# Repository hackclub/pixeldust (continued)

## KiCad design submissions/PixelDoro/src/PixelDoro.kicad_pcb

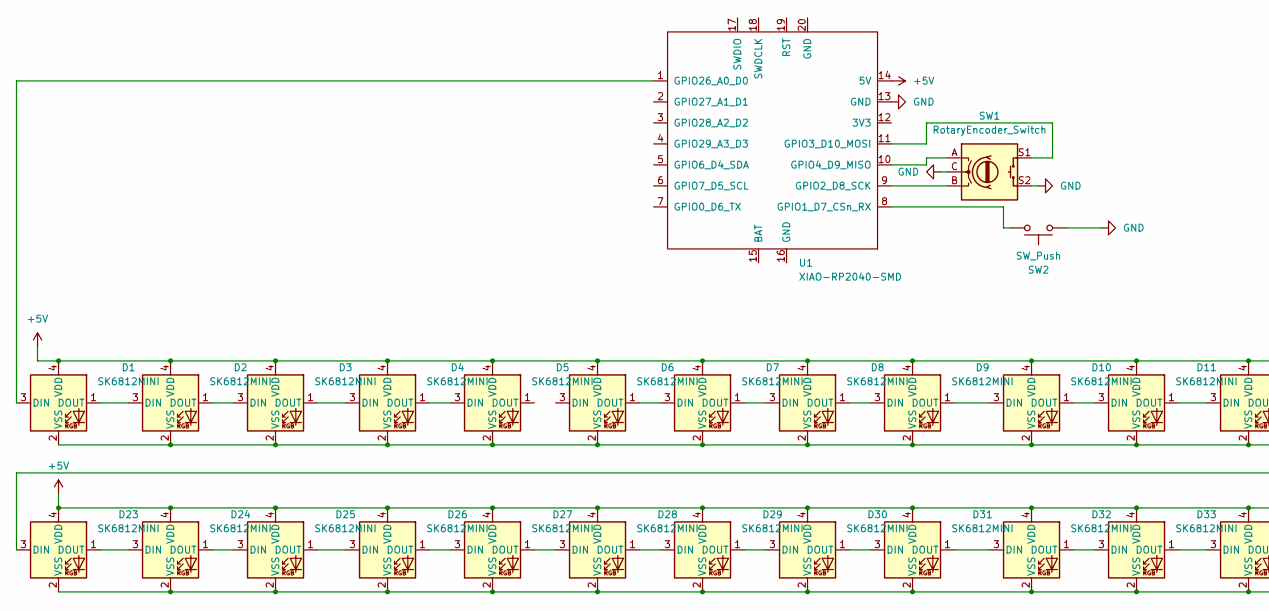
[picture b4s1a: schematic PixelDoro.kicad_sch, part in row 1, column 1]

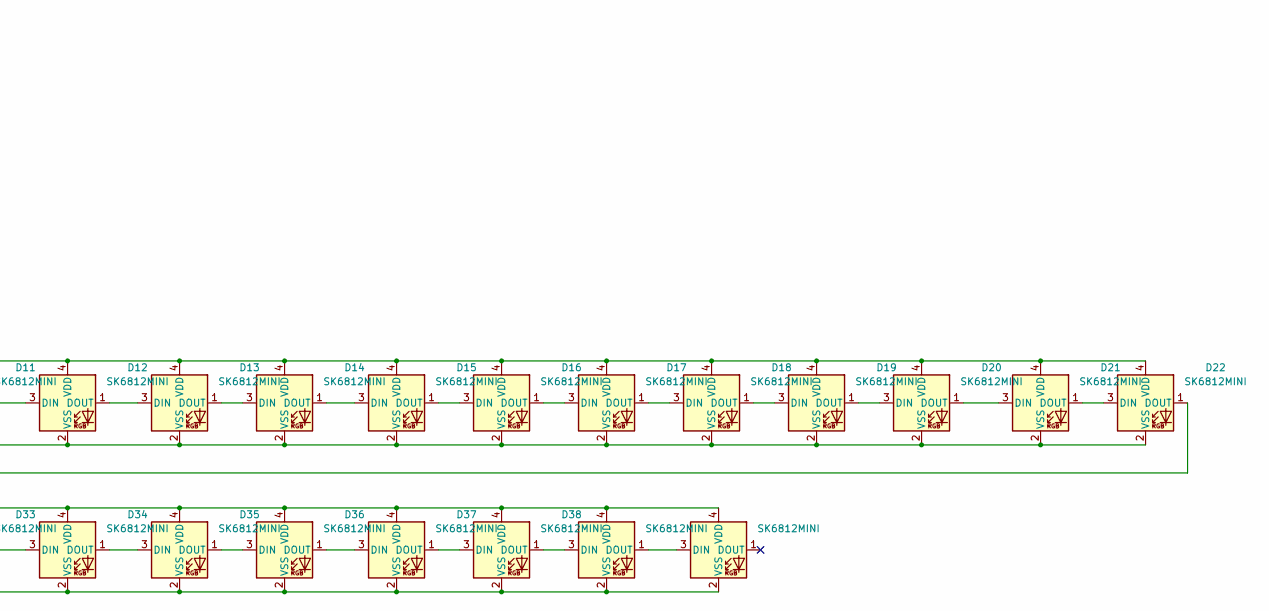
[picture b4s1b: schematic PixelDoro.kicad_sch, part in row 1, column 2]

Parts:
D1, D2, D3, D4, D5, D6, D7, D8, D9, D10, D11, D12, D13, D14, D15, D16, D17, D18, D19, D20, D21, D22, D23, D24, D25, D26, D27, D28, D29, D30, D31, D32, D33, D34, D35, D36, D37, D38, D39, D40: SK6812MINI; LED_SK6812MINI_PLCC4_3.5x3.5mm_P1.75mm
SW1: RotaryEncoder_Switch; RotaryEncoder_Alps_EC11E_Vertical_H20mm_CircularMountingHol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
SW2: SW_Push; SW_PUSH-12mm
U1: XIAO-RP2040-SMD

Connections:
+5V: D1.4 (VDD), D2.4 (VDD), D3.4 (VDD), D4.4 (VDD), D5.4 (VDD), D6.4 (VDD), D7.4 (VDD), D8.4 (VDD), D9.4 (VDD), D10.4 (VDD), D11.4 (VDD), D12.4 (VDD), D13.4 (VDD), D14.4 (VDD), D15.4 (VDD), D16.4 (VDD), D17.4 (VDD), D18.4 (VDD), D19.4 (VDD), D20.4 (VDD), D21.4 (VDD), D22.4 (VDD), D23.4 (VDD), D24.4 (VDD), D25.4 (VDD), D26.4 (VDD), D27.4 (VDD), D28.4 (VDD), D29.4 (VDD), D30.4 (VDD), D31.4 (VDD), D32.4 (VDD), D33.4 (VDD), D34.4 (VDD), D35.4 (VDD), D36.4 (VDD), D37.4 (VDD), D38.4 (VDD), D39.4 (VDD), D40.4 (VDD), U1.14 (5V); also elsewhere on the board
GND: SW1.C, SW1.S2, SW2.1, U1.13 (GND)
unnamed: D1.3 (DIN), U1.1 (GPIO26_A0_D0)
unnamed: D1.1 (DOUT), D2.3 (DIN)
unnamed: D1.2 (VSS), D2.2 (VSS), D3.2 (VSS), D4.2 (VSS), D5.2 (VSS), D6.2 (VSS), D7.2 (VSS), D8.2 (VSS), D9.2 (VSS), D10.2 (VSS), D11.2 (VSS), D12.2 (VSS), D13.2 (VSS), D14.2 (VSS), D15.2 (VSS), D16.2 (VSS), D17.2 (VSS), D18.2 (VSS), D19.2 (VSS), D20.2 (VSS), D21.2 (VSS), D22.2 (VSS)
unnamed: D2.1 (DOUT), D3.3 (DIN)
unnamed: D3.1 (DOUT), D4.3 (DIN)
unnamed: D4.1 (DOUT), D5.3 (DIN)
unnamed: D6.1 (DOUT), D7.3 (DIN)
unnamed: D7.1 (DOUT), D8.3 (DIN)
unnamed: D8.1 (DOUT), D9.3 (DIN)
unnamed: D9.1 (DOUT), D10.3 (DIN)
unnamed: D10.1 (DOUT), D11.3 (DIN)
unnamed: D11.1 (DOUT), D12.3 (DIN)
unnamed: D12.1 (DOUT), D13.3 (DIN)
unnamed: D13.1 (DOUT), D14.3 (DIN)
unnamed: D14.1 (DOUT), D15.3 (DIN)
unnamed: D15.1 (DOUT), D16.3 (DIN)
unnamed: D16.1 (DOUT), D17.3 (DIN)
unnamed: D17.1 (DOUT), D18.3 (DIN)
unnamed: D18.1 (DOUT), D19.3 (DIN)
unnamed: D19.1 (DOUT), D20.3 (DIN)
unnamed: D20.1 (DOUT), D21.3 (DIN)
unnamed: D21.1 (DOUT), D22.3 (DIN)
unnamed: D22.1 (DOUT), D23.3 (DIN)
unnamed: D23.1 (DOUT), D24.3 (DIN)
unnamed 26: D23.2 (VSS), D24.2 (VSS), D25.2 (VSS), D26.2 (VSS), D27.2 (VSS), D28.2 (VSS), D29.2 (VSS), D30.2 (VSS), D31.2 (VSS), D32.2 (VSS), D33.2 (VSS), D34.2 (VSS), D35.2 (VSS), D36.2 (VSS), D37.2 (VSS), D38.2 (VSS), D39.2 (VSS), D40.2 (VSS); also elsewhere on the board
unnamed: D24.1 (DOUT), D25.3 (DIN)
unnamed: D25.1 (DOUT), D26.3 (DIN)
unnamed: D26.1 (DOUT), D27.3 (DIN)
unnamed: D27.1 (DOUT), D28.3 (DIN)
unnamed: D28.1 (DOUT), D29.3 (DIN)
unnamed: D29.1 (DOUT), D30.3 (DIN)
unnamed: D30.1 (DOUT), D31.3 (DIN)
unnamed: D31.1 (DOUT), D32.3 (DIN)
unnamed: D32.1 (DOUT), D33.3 (DIN)
unnamed: D33.1 (DOUT), D34.3 (DIN)
unnamed: D34.1 (DOUT), D35.3 (DIN)
unnamed: D35.1 (DOUT), D36.3 (DIN)
unnamed: D36.1 (DOUT), D37.3 (DIN)
unnamed: D37.1 (DOUT), D38.3 (DIN)
unnamed 41: D38.1 (DOUT), D39.3 (DIN); also elsewhere on the board
unnamed: D39.1 (DOUT), D40.3 (DIN)
unnamed: SW2.2, U1.8 (GPIO1_D7_CSn_RX)
unnamed: SW1.B, U1.9 (GPIO2_D8_SCK)
unnamed: SW1.S1, U1.11 (GPIO3_D10_MOSI)
unnamed: SW1.A, U1.10 (GPIO4_D9_MISO)

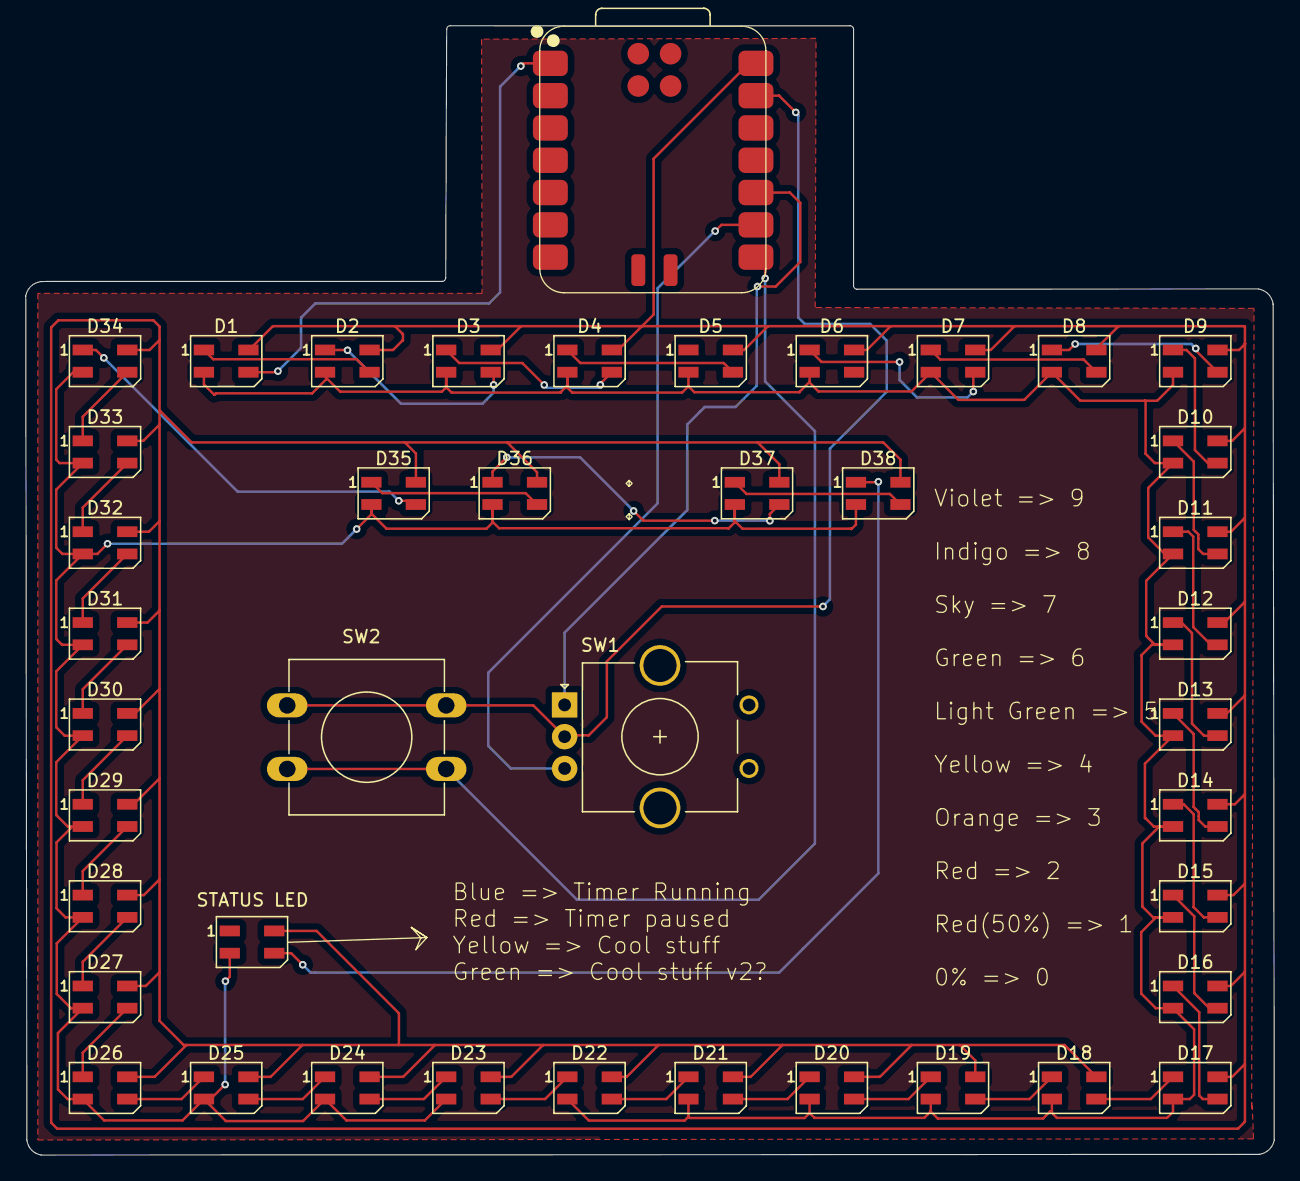
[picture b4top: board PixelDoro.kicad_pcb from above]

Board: 2 copper layers, 98.2 x 88.8 mm, 42 parts (0 on the bottom side), 45 nets.

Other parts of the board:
STATUS LED: Status LED; LED_SK6812MINI_PLCC4_3.5x3.5mm_P1.75mm

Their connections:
+5V: STATUS LED.4 (VDD); also elsewhere on the board
unnamed 26: STATUS LED.2 (VSS); also elsewhere on the board
unnamed 41: STATUS LED.3 (DIN); also elsewhere on the board

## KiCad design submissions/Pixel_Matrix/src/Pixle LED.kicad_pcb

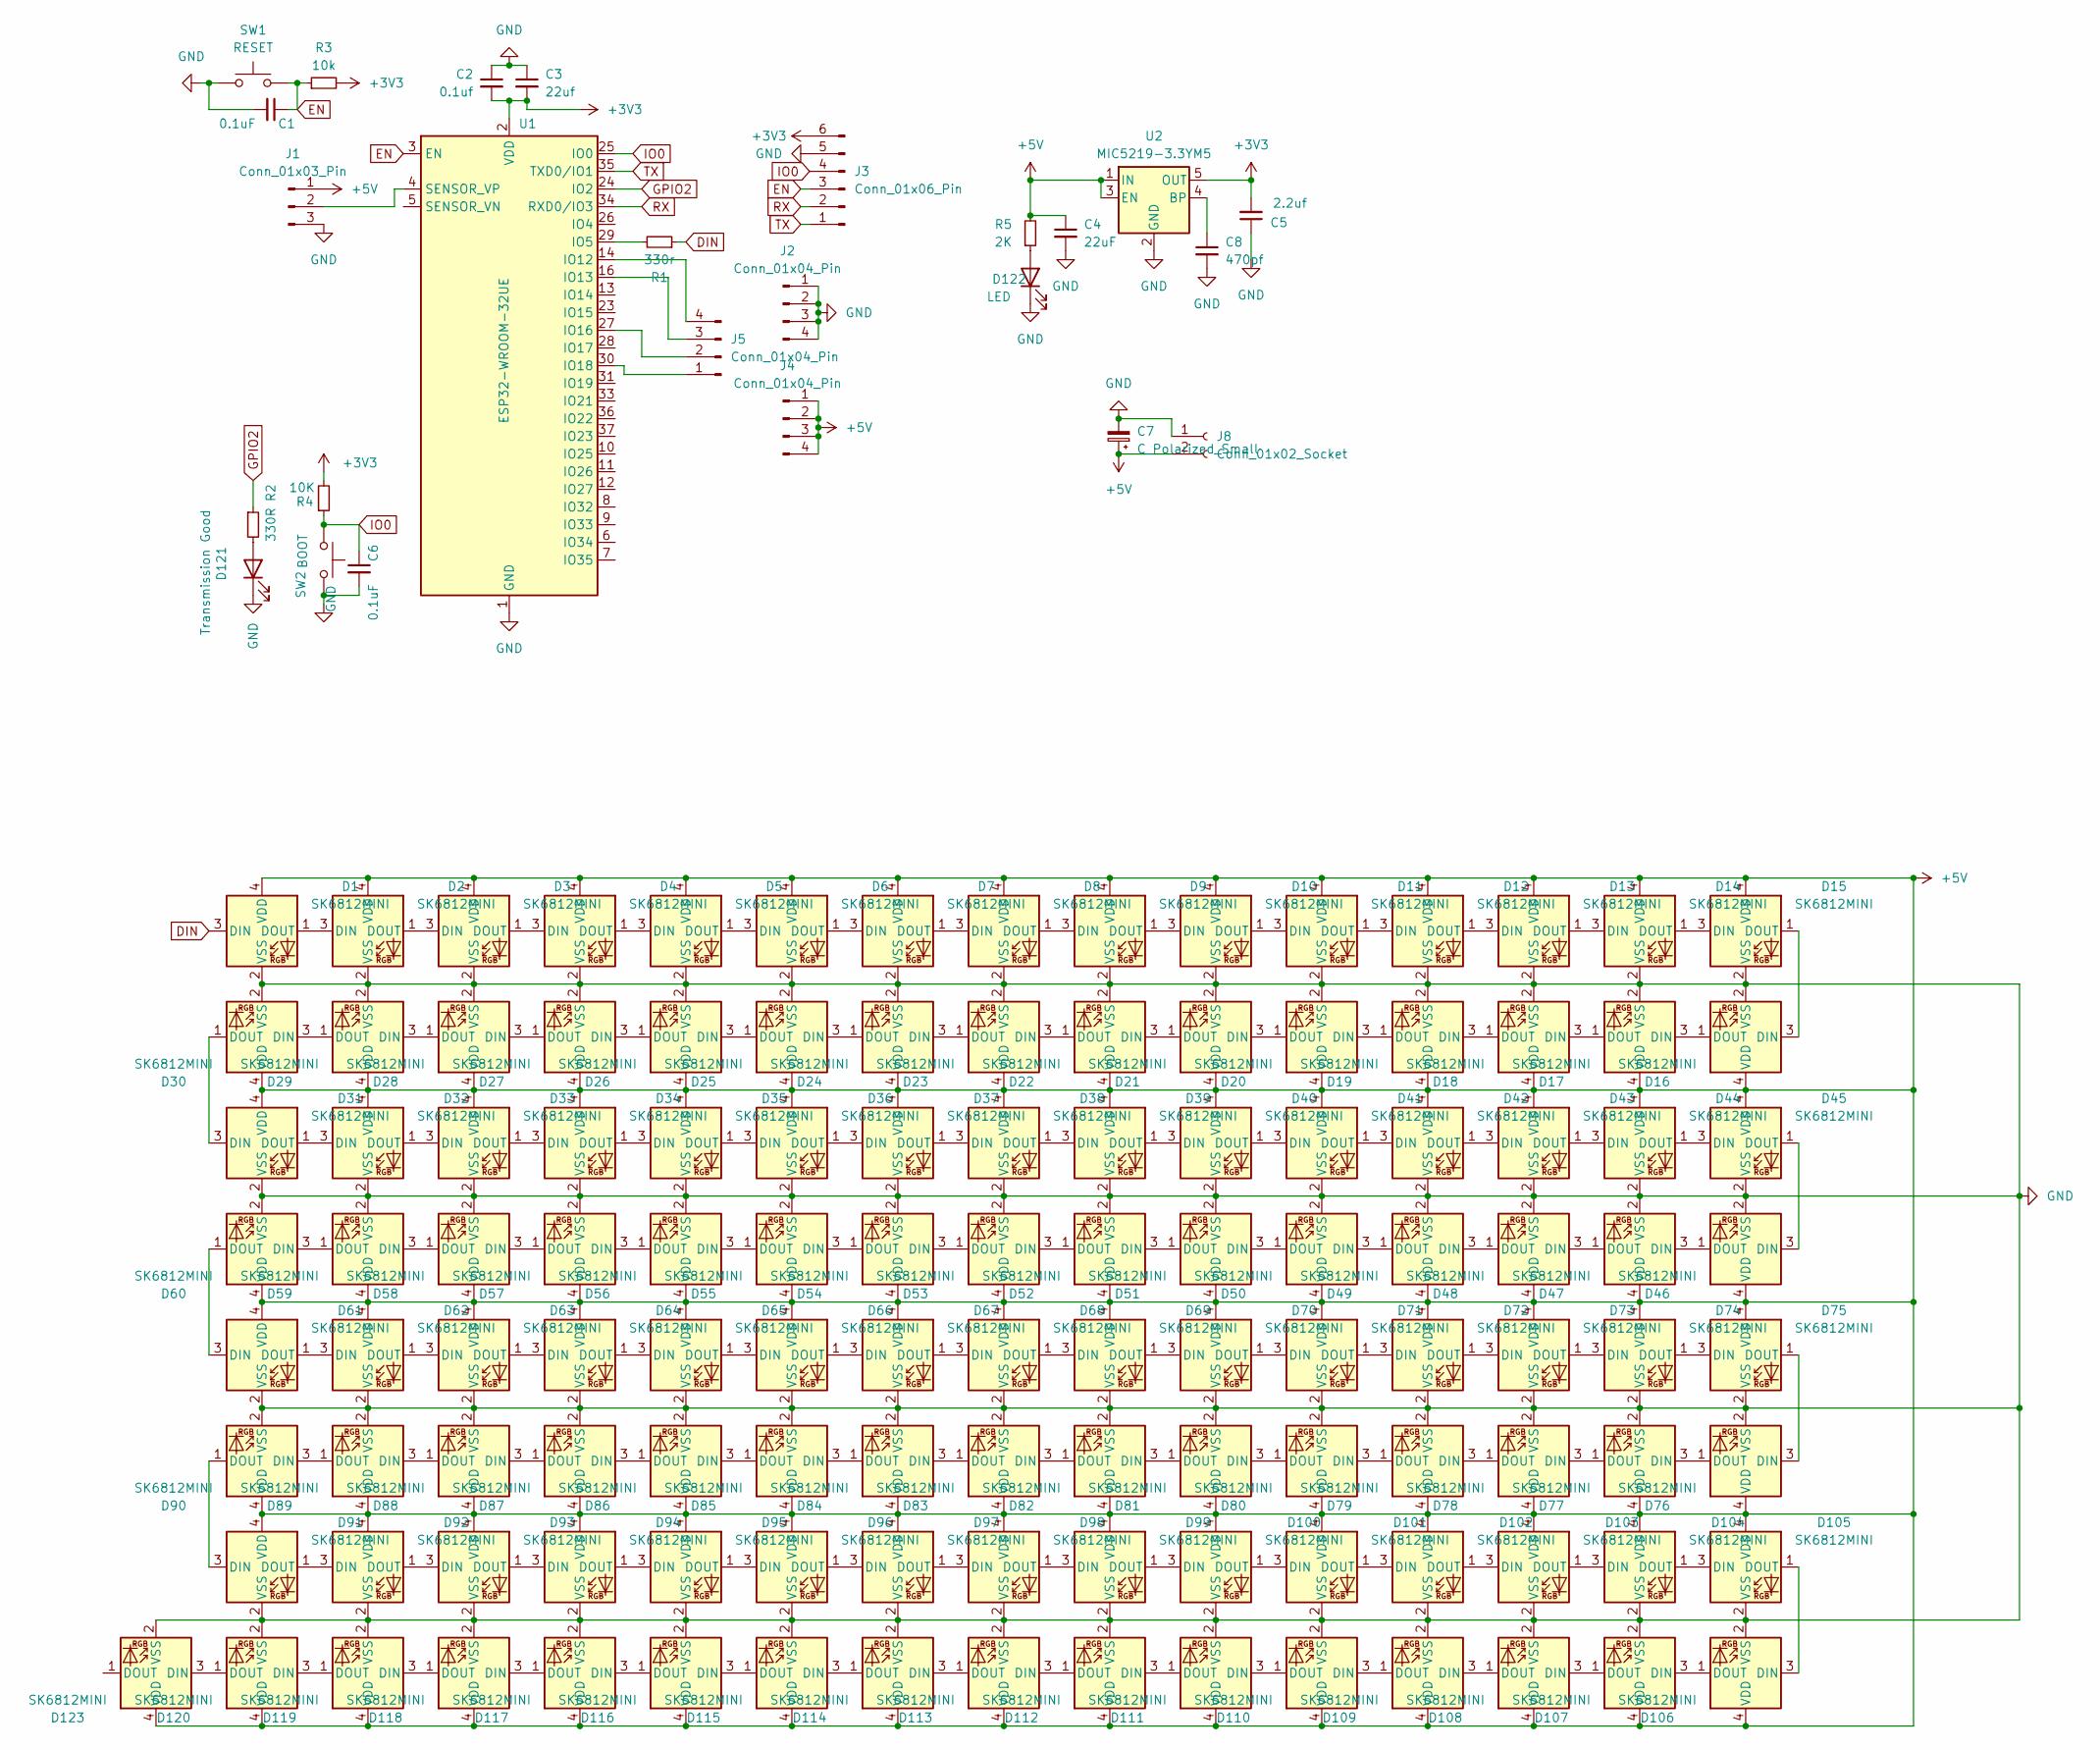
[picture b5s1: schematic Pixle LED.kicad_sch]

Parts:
C1, C6: 0.1uF; C_0805_2012Metric_Pad1.18x1.45mm_HandSolder
C2: 0.1uf; C_0805_2012Metric_Pad1.18x1.45mm_HandSolder
C3: 22uf; C_0805_2012Metric_Pad1.18x1.45mm_HandSolder
C4: 22uF; C_0805_2012Metric_Pad1.18x1.45mm_HandSolder
C5: 2.2uf; C_0603_1608Metric_Pad1.08x0.95mm_HandSolder
C7: C_Polarized_Small; CP_Radial_D8.0mm_P3.50mm
C8: 470pf; C_0603_1608Metric_Pad1.08x0.95mm_HandSolder
D1, D2, D3, D4, D5, D6, D7, D8, D9, D10, D11, D12, D13, D14, D15, D16, D17, D18, D19, D20, D21, D22, D23, D24, D25, D26, D27, D28, D29, D30, D31, D32, D33, D34, D35, D36, D37, D38, D39, D40, D41, D42, D43, D44, D45, D46, D47, D48, D49, D50, D51, D52, D53, D54, D55, D56, D57, D58, D59, D60, D61, D62, D63, D64, D65, D66, D67, D68, D69, D70, D71, D72, D73, D74, D75, D76, D77, D78, D79, D80, D81, D82, D83, D84, D85, D86, D87, D88, D89, D90, D91, D92, D93, D94, D95, D96, D97, D98, D99, D100, D101, D102, D103, D104, D105, D106, D107, D108, D109, D110, D111, D112, D113, D114, D115, D116, D117, D118, D119, D120, D123: SK6812MINI; LED_SK6812MINI_PLCC4_3.5x3.5mm_P1.75mm
D121: Transmission Good; LED_0805_2012Metric_Pad1.15x1.40mm_HandSolder
D122: LED; LED_0805_2012Metric_Pad1.15x1.40mm_HandSolder
J1: Conn_01x03_Pin; PinHeader_1x03_P2.54mm_Vertical
J2, J4, J5: Conn_01x04_Pin; PinHeader_1x04_P2.54mm_Vertical
J3: Conn_01x06_Pin; PinHeader_1x06_P2.54mm_Vertical
J8: Conn_01x02_Socket; TerminalBlock_MaiXu_MX126-5.0-02P_1x02_P5.00mm
R1: 330r; R_0603_1608Metric_Pad0.98x0.95mm_HandSolder
R2: 330R; R_0805_2012Metric_Pad1.20x1.40mm_HandSolder
R3: 10k; R_0805_2012Metric_Pad1.20x1.40mm_HandSolder
R4: 10K; R_0805_2012Metric_Pad1.20x1.40mm_HandSolder
R5: 2K; R_0805_2012Metric_Pad1.20x1.40mm_HandSolder
SW1: RESET; SW_Push_SPST_NO_Alps_SKRK
SW2: BOOT; SW_Push_SPST_NO_Alps_SKRK
U1: ESP32-WROOM-32UE; ESP32-WROOM-32E
U2: MIC5219-3.3YM5; SOT-23-5

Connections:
+3V3: C2.2, C3.2, C5.2, J3.6, R3.2, R4.2, U1.2 (VDD), U2.5 (OUT)
+5V: C4.1, C7.1, D1.4 (VDD), D2.4 (VDD), D3.4 (VDD), D4.4 (VDD), D5.4 (VDD), D6.4 (VDD), D7.4 (VDD), D8.4 (VDD), D9.4 (VDD), D10.4 (VDD), D11.4 (VDD), D12.4 (VDD), D13.4 (VDD), D14.4 (VDD), D15.4 (VDD), D16.4 (VDD), D17.4 (VDD), D18.4 (VDD), D19.4 (VDD), D20.4 (VDD), D21.4 (VDD), D22.4 (VDD), D23.4 (VDD), D24.4 (VDD), D25.4 (VDD), D26.4 (VDD), D27.4 (VDD), D28.4 (VDD), D29.4 (VDD), D30.4 (VDD), D31.4 (VDD), D32.4 (VDD), D33.4 (VDD), D34.4 (VDD), D35.4 (VDD), D36.4 (VDD), D37.4 (VDD), D38.4 (VDD), D39.4 (VDD), D40.4 (VDD), D41.4 (VDD), D42.4 (VDD), D43.4 (VDD), D44.4 (VDD), D45.4 (VDD), D46.4 (VDD), D47.4 (VDD), D48.4 (VDD), D49.4 (VDD), D50.4 (VDD), D51.4 (VDD), D52.4 (VDD), D53.4 (VDD), D54.4 (VDD), D55.4 (VDD), D56.4 (VDD), D57.4 (VDD), D58.4 (VDD), D59.4 (VDD), D60.4 (VDD), D61.4 (VDD), D62.4 (VDD), D63.4 (VDD), D64.4 (VDD), D65.4 (VDD), D66.4 (VDD), D67.4 (VDD), D68.4 (VDD), D69.4 (VDD), D70.4 (VDD), D71.4 (VDD), D72.4 (VDD), D73.4 (VDD), D74.4 (VDD), D75.4 (VDD), D76.4 (VDD), D77.4 (VDD), D78.4 (VDD), D79.4 (VDD), D80.4 (VDD), D81.4 (VDD), D82.4 (VDD), D83.4 (VDD), D84.4 (VDD), D85.4 (VDD), D86.4 (VDD), D87.4 (VDD), D88.4 (VDD), D89.4 (VDD), D90.4 (VDD), D91.4 (VDD), D92.4 (VDD), D93.4 (VDD), D94.4 (VDD), D95.4 (VDD), D96.4 (VDD), D97.4 (VDD), D98.4 (VDD), D99.4 (VDD), D100.4 (VDD), D101.4 (VDD), D102.4 (VDD), D103.4 (VDD), D104.4 (VDD), D105.4 (VDD), D106.4 (VDD), D107.4 (VDD), D108.4 (VDD), D109.4 (VDD), D110.4 (VDD), D111.4 (VDD), D112.4 (VDD), D113.4 (VDD), D114.4 (VDD), D115.4 (VDD), D116.4 (VDD), D117.4 (VDD), D118.4 (VDD), D119.4 (VDD), D120.4 (VDD), D123.4 (VDD), J1.1, J4.1, J4.2, J4.3, J4.4, J8.2, R5.2, U2.1 (IN), U2.3 (EN)
DIN: D1.3 (DIN), R1.1
EN: C1.1, J3.3, R3.1, SW1.2, U1.3 (EN)
GND: C1.2, C2.1, C3.1, C4.2, C5.1, C6.2, C7.2, C8.2, D1.2 (VSS), D2.2 (VSS), D3.2 (VSS), D4.2 (VSS), D5.2 (VSS), D6.2 (VSS), D7.2 (VSS), D8.2 (VSS), D9.2 (VSS), D10.2 (VSS), D11.2 (VSS), D12.2 (VSS), D13.2 (VSS), D14.2 (VSS), D15.2 (VSS), D16.2 (VSS), D17.2 (VSS), D18.2 (VSS), D19.2 (VSS), D20.2 (VSS), D21.2 (VSS), D22.2 (VSS), D23.2 (VSS), D24.2 (VSS), D25.2 (VSS), D26.2 (VSS), D27.2 (VSS), D28.2 (VSS), D29.2 (VSS), D30.2 (VSS), D31.2 (VSS), D32.2 (VSS), D33.2 (VSS), D34.2 (VSS), D35.2 (VSS), D36.2 (VSS), D37.2 (VSS), D38.2 (VSS), D39.2 (VSS), D40.2 (VSS), D41.2 (VSS), D42.2 (VSS), D43.2 (VSS), D44.2 (VSS), D45.2 (VSS), D46.2 (VSS), D47.2 (VSS), D48.2 (VSS), D49.2 (VSS), D50.2 (VSS), D51.2 (VSS), D52.2 (VSS), D53.2 (VSS), D54.2 (VSS), D55.2 (VSS), D56.2 (VSS), D57.2 (VSS), D58.2 (VSS), D59.2 (VSS), D60.2 (VSS), D61.2 (VSS), D62.2 (VSS), D63.2 (VSS), D64.2 (VSS), D65.2 (VSS), D66.2 (VSS), D67.2 (VSS), D68.2 (VSS), D69.2 (VSS), D70.2 (VSS), D71.2 (VSS), D72.2 (VSS), D73.2 (VSS), D74.2 (VSS), D75.2 (VSS), D76.2 (VSS), D77.2 (VSS), D78.2 (VSS), D79.2 (VSS), D80.2 (VSS), D81.2 (VSS), D82.2 (VSS), D83.2 (VSS), D84.2 (VSS), D85.2 (VSS), D86.2 (VSS), D87.2 (VSS), D88.2 (VSS), D89.2 (VSS), D90.2 (VSS), D91.2 (VSS), D92.2 (VSS), D93.2 (VSS), D94.2 (VSS), D95.2 (VSS), D96.2 (VSS), D97.2 (VSS), D98.2 (VSS), D99.2 (VSS), D100.2 (VSS), D101.2 (VSS), D102.2 (VSS), D103.2 (VSS), D104.2 (VSS), D105.2 (VSS), D106.2 (VSS), D107.2 (VSS), D108.2 (VSS), D109.2 (VSS), D110.2 (VSS), D111.2 (VSS), D112.2 (VSS), D113.2 (VSS), D114.2 (VSS), D115.2 (VSS), D116.2 (VSS), D117.2 (VSS), D118.2 (VSS), D119.2 (VSS), D120.2 (VSS), D121.1 (K), D122.1 (K), D123.2 (VSS), J1.3, J2.1, J2.2, J2.3, J2.4, J3.5, J8.1, SW1.1, SW2.2, U1.1 (GND), U1.15 (GND), U1.38 (GND), U1.39 (GND), U2.2 (GND)
GPIO2: R2.1, U1.24 (IO2)
IO0: C6.1, J3.4, R4.1, SW2.1, U1.25 (IO0)
unnamed: D1.1 (DOUT), D2.3 (DIN)
unnamed: D2.1 (DOUT), D3.3 (DIN)
unnamed: D3.1 (DOUT), D4.3 (DIN)
unnamed: D4.1 (DOUT), D5.3 (DIN)
unnamed: D5.1 (DOUT), D6.3 (DIN)
unnamed: D6.1 (DOUT), D7.3 (DIN)
unnamed: D7.1 (DOUT), D8.3 (DIN)
unnamed: D8.1 (DOUT), D9.3 (DIN)
unnamed: D9.1 (DOUT), D10.3 (DIN)
unnamed: D10.1 (DOUT), D11.3 (DIN)
unnamed: D11.1 (DOUT), D12.3 (DIN)
unnamed: D12.1 (DOUT), D13.3 (DIN)
unnamed: D13.1 (DOUT), D14.3 (DIN)
unnamed: D14.1 (DOUT), D15.3 (DIN)
unnamed: D15.1 (DOUT), D16.3 (DIN)
unnamed: D16.1 (DOUT), D17.3 (DIN)
unnamed: D17.1 (DOUT), D18.3 (DIN)
unnamed: D18.1 (DOUT), D19.3 (DIN)
unnamed: D19.1 (DOUT), D20.3 (DIN)
unnamed: D20.1 (DOUT), D21.3 (DIN)
unnamed: D21.1 (DOUT), D22.3 (DIN)
unnamed: D22.1 (DOUT), D23.3 (DIN)
unnamed: D23.1 (DOUT), D24.3 (DIN)
unnamed: D24.1 (DOUT), D25.3 (DIN)
unnamed: D25.1 (DOUT), D26.3 (DIN)
unnamed: D26.1 (DOUT), D27.3 (DIN)
unnamed: D27.1 (DOUT), D28.3 (DIN)
unnamed: D28.1 (DOUT), D29.3 (DIN)
unnamed: D29.1 (DOUT), D30.3 (DIN)
unnamed: D30.1 (DOUT), D31.3 (DIN)
unnamed: D31.1 (DOUT), D32.3 (DIN)
unnamed: D32.1 (DOUT), D33.3 (DIN)
unnamed: D33.1 (DOUT), D34.3 (DIN)
unnamed: D34.1 (DOUT), D35.3 (DIN)
unnamed: D35.1 (DOUT), D36.3 (DIN)
unnamed: D36.1 (DOUT), D37.3 (DIN)
unnamed: D37.1 (DOUT), D38.3 (DIN)
unnamed: D38.1 (DOUT), D39.3 (DIN)
unnamed: D39.1 (DOUT), D40.3 (DIN)
unnamed: D40.1 (DOUT), D41.3 (DIN)
unnamed: D41.1 (DOUT), D42.3 (DIN)
unnamed: D42.1 (DOUT), D43.3 (DIN)
unnamed: D43.1 (DOUT), D44.3 (DIN)
unnamed: D44.1 (DOUT), D45.3 (DIN)
unnamed: D45.1 (DOUT), D46.3 (DIN)
unnamed: D46.1 (DOUT), D47.3 (DIN)
unnamed: D47.1 (DOUT), D48.3 (DIN)
unnamed: D48.1 (DOUT), D49.3 (DIN)
unnamed: D49.1 (DOUT), D50.3 (DIN)
unnamed: D50.1 (DOUT), D51.3 (DIN)
unnamed: D51.1 (DOUT), D52.3 (DIN)
unnamed: D52.1 (DOUT), D53.3 (DIN)
unnamed: D53.1 (DOUT), D54.3 (DIN)
unnamed: D54.1 (DOUT), D55.3 (DIN)
unnamed: D55.1 (DOUT), D56.3 (DIN)
unnamed: D56.1 (DOUT), D57.3 (DIN)
unnamed: D57.1 (DOUT), D58.3 (DIN)
unnamed: D58.1 (DOUT), D59.3 (DIN)
unnamed: D59.1 (DOUT), D60.3 (DIN)
unnamed: D60.1 (DOUT), D61.3 (DIN)
unnamed: D61.1 (DOUT), D62.3 (DIN)
unnamed: D62.1 (DOUT), D63.3 (DIN)
unnamed: D63.1 (DOUT), D64.3 (DIN)
unnamed: D64.1 (DOUT), D65.3 (DIN)
unnamed: D65.1 (DOUT), D66.3 (DIN)
unnamed: D66.1 (DOUT), D67.3 (DIN)
unnamed: D67.1 (DOUT), D68.3 (DIN)
unnamed: D68.1 (DOUT), D69.3 (DIN)
unnamed: D69.1 (DOUT), D70.3 (DIN)
unnamed: D70.1 (DOUT), D71.3 (DIN)
unnamed: D71.1 (DOUT), D72.3 (DIN)
unnamed: D72.1 (DOUT), D73.3 (DIN)
unnamed: D73.1 (DOUT), D74.3 (DIN)
unnamed: D74.1 (DOUT), D75.3 (DIN)
unnamed: D75.1 (DOUT), D76.3 (DIN)
unnamed: D76.1 (DOUT), D77.3 (DIN)
unnamed: D77.1 (DOUT), D78.3 (DIN)
unnamed: D78.1 (DOUT), D79.3 (DIN)
unnamed: D79.1 (DOUT), D80.3 (DIN)
unnamed: D80.1 (DOUT), D81.3 (DIN)
unnamed: D81.1 (DOUT), D82.3 (DIN)
unnamed: D82.1 (DOUT), D83.3 (DIN)
unnamed: D83.1 (DOUT), D84.3 (DIN)
unnamed: D84.1 (DOUT), D85.3 (DIN)
unnamed: D85.1 (DOUT), D86.3 (DIN)
unnamed: D86.1 (DOUT), D87.3 (DIN)
unnamed: D87.1 (DOUT), D88.3 (DIN)
unnamed: D88.1 (DOUT), D89.3 (DIN)
unnamed: D89.1 (DOUT), D90.3 (DIN)
unnamed: D90.1 (DOUT), D91.3 (DIN)
unnamed: D91.1 (DOUT), D92.3 (DIN)
unnamed: D92.1 (DOUT), D93.3 (DIN)
unnamed: D93.1 (DOUT), D94.3 (DIN)
unnamed: D94.1 (DOUT), D95.3 (DIN)
unnamed: D95.1 (DOUT), D96.3 (DIN)
unnamed: D96.1 (DOUT), D97.3 (DIN)
unnamed: D97.1 (DOUT), D98.3 (DIN)
unnamed: D98.1 (DOUT), D99.3 (DIN)
unnamed: D99.1 (DOUT), D100.3 (DIN)
unnamed: D100.1 (DOUT), D101.3 (DIN)
unnamed: D101.1 (DOUT), D102.3 (DIN)
unnamed: D102.1 (DOUT), D103.3 (DIN)
unnamed: D103.1 (DOUT), D104.3 (DIN)
unnamed: D104.1 (DOUT), D105.3 (DIN)
unnamed: D105.1 (DOUT), D106.3 (DIN)
unnamed: D106.1 (DOUT), D107.3 (DIN)
unnamed: D107.1 (DOUT), D108.3 (DIN)
unnamed: D108.1 (DOUT), D109.3 (DIN)
unnamed: D109.1 (DOUT), D110.3 (DIN)
unnamed: D110.1 (DOUT), D111.3 (DIN)
unnamed: D111.1 (DOUT), D112.3 (DIN)
unnamed: D112.1 (DOUT), D113.3 (DIN)
unnamed: D113.1 (DOUT), D114.3 (DIN)
unnamed: D114.1 (DOUT), D115.3 (DIN)
unnamed: D115.1 (DOUT), D116.3 (DIN)
unnamed: D116.1 (DOUT), D117.3 (DIN)
unnamed: D117.1 (DOUT), D118.3 (DIN)
unnamed: D118.1 (DOUT), D119.3 (DIN)
unnamed: D119.1 (DOUT), D120.3 (DIN)
unnamed: D120.1 (DOUT), D123.3 (DIN)
unnamed: D121.2 (A), R2.2
unnamed: D122.2 (A), R5.1
unnamed: J1.2, U1.4 (SENSOR_VP)
unnamed: J5.1, U1.30 (IO18)
unnamed: J5.2, U1.27 (IO16)
unnamed: J5.3, U1.16 (IO13)
unnamed: J5.4, U1.14 (IO12)
unnamed: R1.2, U1.29 (IO5)
unnamed: C8.1, U2.4 (BP)
RX: J3.2, U1.34 (RXD0/IO3)
TX: J3.1, U1.35 (TXD0/IO1)

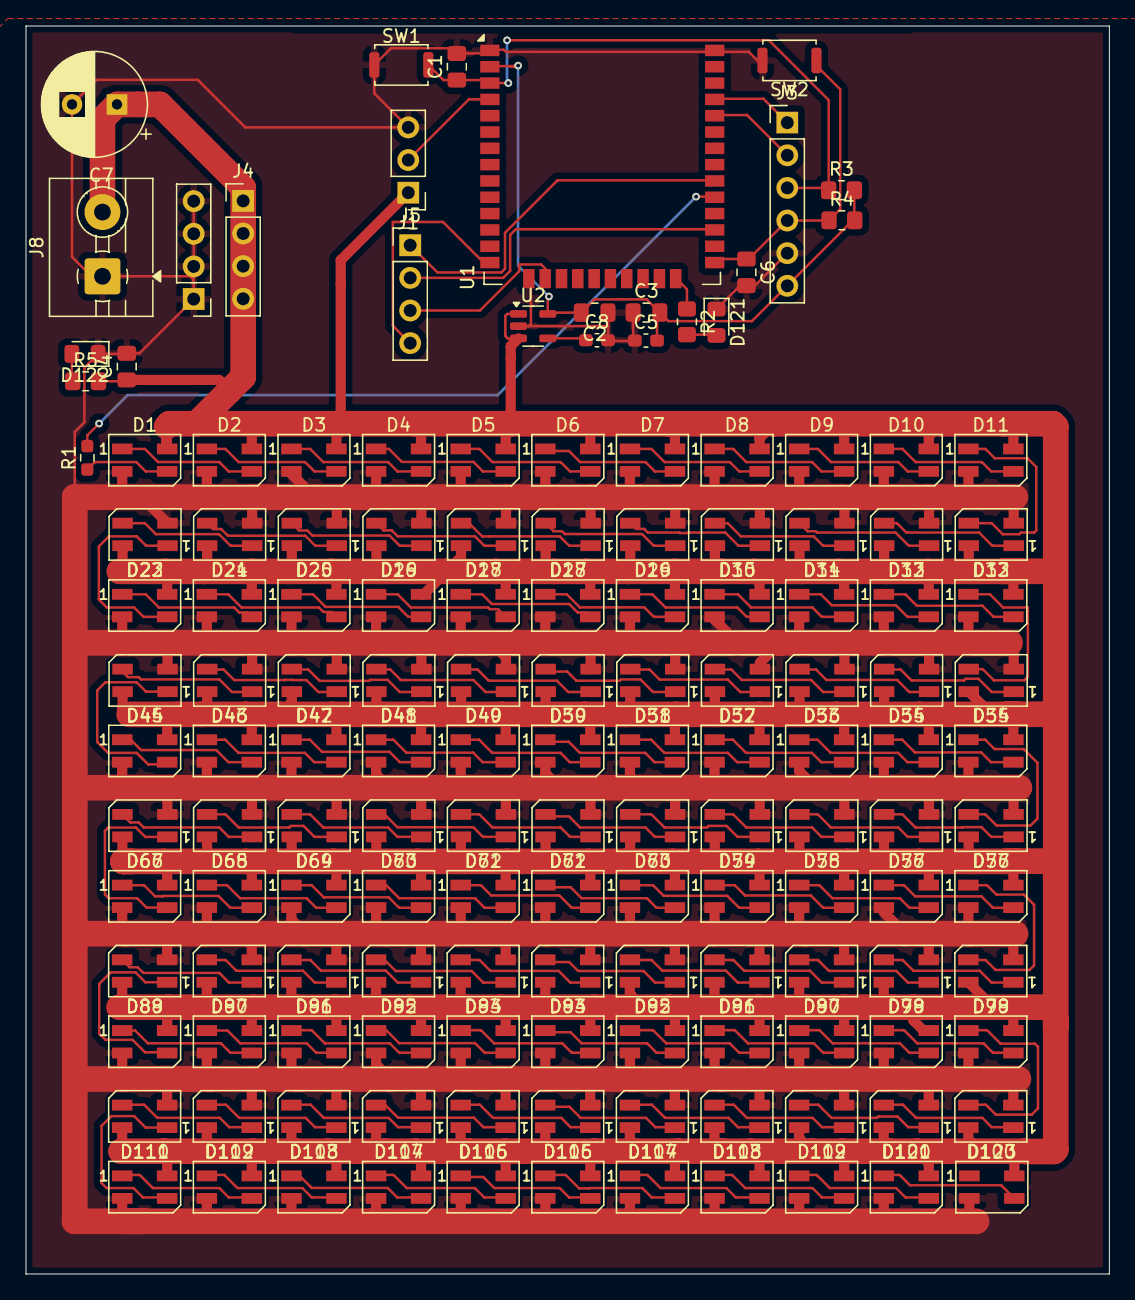
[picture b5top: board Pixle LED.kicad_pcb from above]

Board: 2 copper layers, 84.3 x 97.1 mm, 146 parts (0 on the bottom side), 138 nets.
